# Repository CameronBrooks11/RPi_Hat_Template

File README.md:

# rpi-hat-kicad

KiCad 10 project templates for a Raspberry Pi
[HAT+](https://datasheets.raspberrypi.com/hat/hat-plus-specification.pdf): the
board outline, mounting holes, 40-pin GPIO connector and the ID EEPROM a HAT+
needs, placed, routed and passing DRC, ready to design on.

**Documentation: <https://cameronbrooks11.github.io/rpi-hat-kicad/>**

| Template                      | GPIO connector                                 | Board         |
| ----------------------------- | ---------------------------------------------- | ------------- |
| [`RPi_Hat_THT`](RPi_Hat_THT/) | 2x20 through-hole female header, underneath    | 65 x 56 mm    |
| [`RPi_Hat_SMD`](RPi_Hat_SMD/) | Samtec HLE-120-02 SMD pass-through socket      | 65 x 56.5 mm  |

Each template has the outline from Raspberry Pi's HAT mechanical drawing, four
mounting holes, the GPIO connector J1 with its power pins wired and a global
label (`GPIO2` to `GPIO27`) on every other GPIO pin, and the HAT+ ID EEPROM
placed and routed beside J1. Each carries its own `RPi_Hat` libraries, so a
project opens without installing anything.

- **New HAT:** [create a project from a template](https://cameronbrooks11.github.io/rpi-hat-kicad/getting-started/).
- **Which template:** [through-hole or SMD](https://cameronbrooks11.github.io/rpi-hat-kicad/templates/); it decides how high the board sits above the Pi.
- **Calling it a HAT+:** the [HAT+ checklist](https://cameronbrooks11.github.io/rpi-hat-kicad/hat-plus/) and [programming the ID EEPROM](https://cameronbrooks11.github.io/rpi-hat-kicad/eeprom/).

## Development

With [just](https://just.systems/), Python 3 and KiCad 10's `kicad-cli`,
`just check` is the gate CI runs on every pull request: the two templates'
libraries identical, ERC finding only the 26 GPIO label warnings, and DRC
clean with schematic parity on both. The
[development page](https://cameronbrooks11.github.io/rpi-hat-kicad/development/)
covers changing a template and building the docs.

## Credit

Derived from [RPi_Hat_Template](https://github.com/devbisme/RPi_Hat_Template)
by Dave Vandenbout, which laid both connectors and both outlines over each
other for the user to delete one. The footprints come from his
[RPi_Hat.pretty](https://github.com/devbisme/RPi_Hat.pretty).

## License

MIT. See [LICENSE](LICENSE).

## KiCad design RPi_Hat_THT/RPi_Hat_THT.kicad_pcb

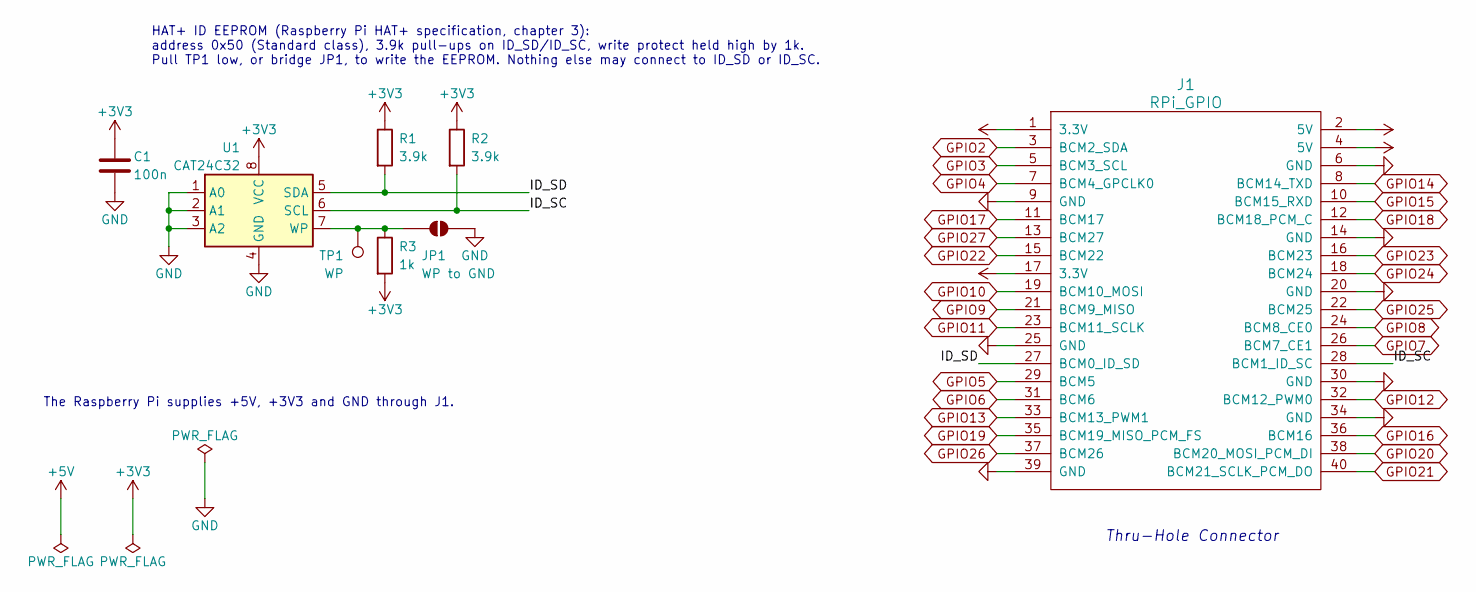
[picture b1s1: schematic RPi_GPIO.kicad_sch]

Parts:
C1: 100n; C_0603_1608Metric
J1: RPi_GPIO; Pin_Header_Straight_2x20
JP1: WP to GND; SolderJumper-2_P1.3mm_Open_RoundedPad1.0x1.5mm
R1, R2: 3.9k; R_0603_1608Metric
R3: 1k; R_0603_1608Metric
TP1: WP; TestPoint_Pad_D1.0mm
U1: CAT24C32; SOIC-8_3.9x4.9mm_P1.27mm

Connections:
+3V3: C1.1, J1.1 (3.3V), J1.17 (3.3V), R1.1, R2.1, R3.2, U1.8 (VCC)
+5V: J1.2 (5V), J1.4 (5V)
/RPi_GPIO/ID_SC: J1.28 (BCM1_ID_SC), R2.2, U1.6 (SCL)
/RPi_GPIO/ID_SD: J1.27 (BCM0_ID_SD), R1.2, U1.5 (SDA)
GND: C1.2, J1.6 (GND), J1.9 (GND), J1.14 (GND), J1.20 (GND), J1.25 (GND), J1.30 (GND), J1.34 (GND), J1.39 (GND), JP1.2 (B), U1.1 (A0), U1.2 (A1), U1.3 (A2), U1.4 (GND)
GPIO2: J1.3 (BCM2_SDA)
GPIO3: J1.5 (BCM3_SCL)
GPIO4: J1.7 (BCM4_GPCLK0)
GPIO5: J1.29 (BCM5)
GPIO6: J1.31 (BCM6)
GPIO7: J1.26 (BCM7_CE1)
GPIO8: J1.24 (BCM8_CE0)
GPIO9: J1.21 (BCM9_MISO)
GPIO10: J1.19 (BCM10_MOSI)
GPIO11: J1.23 (BCM11_SCLK)
GPIO12: J1.32 (BCM12_PWM0)
GPIO13: J1.33 (BCM13_PWM1)
GPIO14: J1.8 (BCM14_TXD)
GPIO15: J1.10 (BCM15_RXD)
GPIO16: J1.36 (BCM16)
GPIO17: J1.11 (BCM17)
GPIO18: J1.12 (BCM18_PCM_C)
GPIO19: J1.35 (BCM19_MISO_PCM_FS)
GPIO20: J1.38 (BCM20_MOSI_PCM_DI)
GPIO21: J1.40 (BCM21_SCLK_PCM_DO)
GPIO22: J1.15 (BCM22)
GPIO23: J1.16 (BCM23)
GPIO24: J1.18 (BCM24)
GPIO25: J1.22 (BCM25)
GPIO26: J1.37 (BCM26)
GPIO27: J1.13 (BCM27)
unnamed: JP1.1 (A), R3.1, TP1.1, U1.7 (WP)

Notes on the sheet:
Thru-Hole Connector
HAT+ ID EEPROM (Raspberry Pi HAT+ specification, chapter 3): address 0x50 (Standard class), 3.9k pull-ups on ID_SD/ID_SC, write protect held high by 1k. Pull TP1 low, or bridge JP1, to write the EEPROM. Nothing else may connect to ID_SD or ID_SC.
The Raspberry Pi supplies +5V, +3V3 and GND through J1.

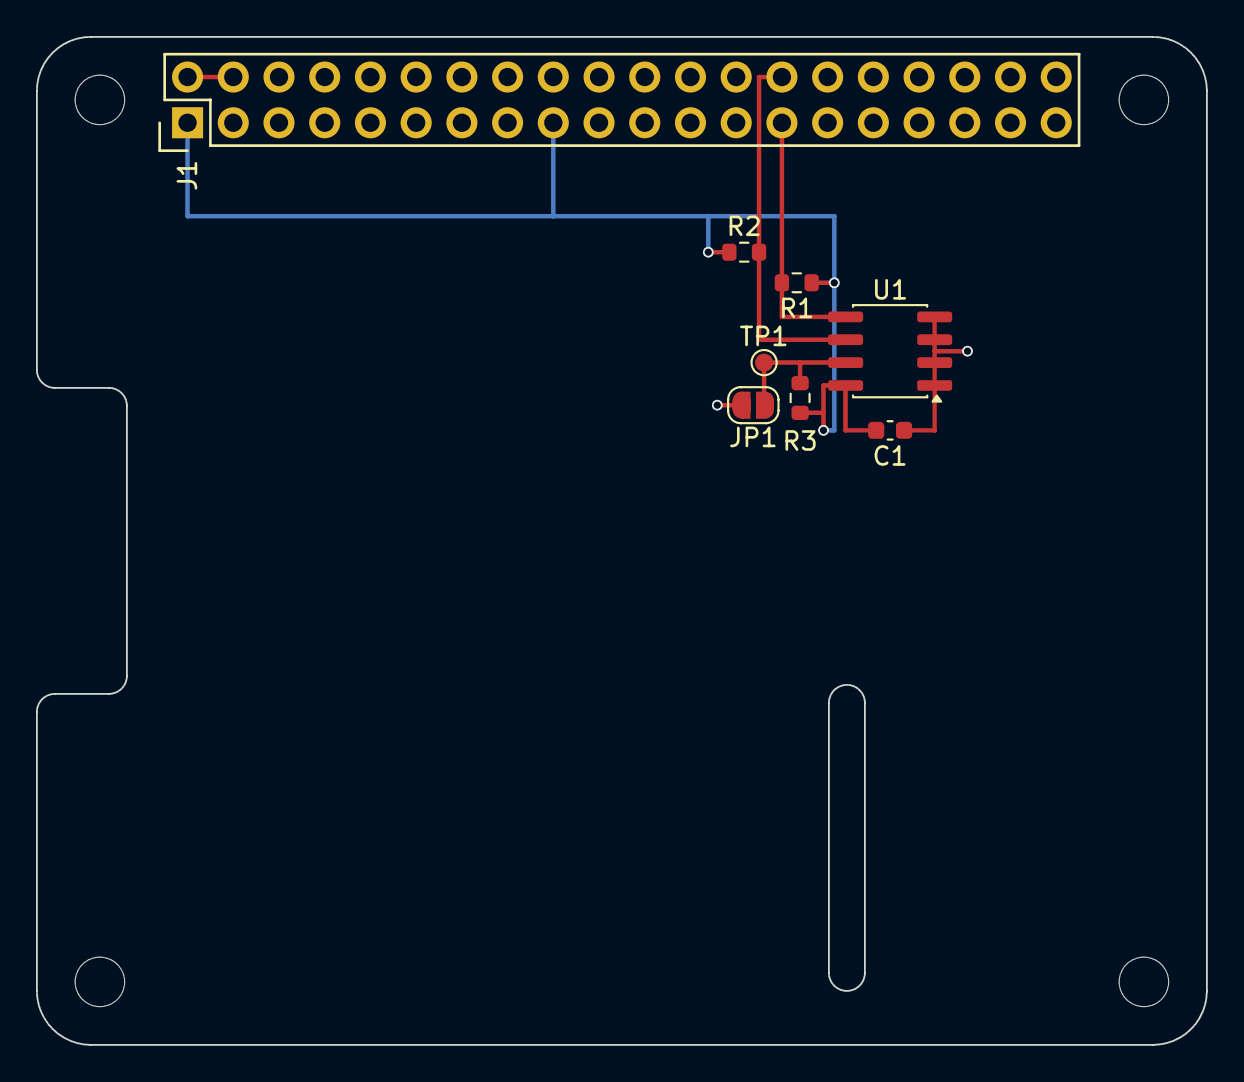
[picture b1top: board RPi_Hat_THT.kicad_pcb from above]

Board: 2 copper layers, 65.0 x 56.0 mm, 12 parts (0 on the bottom side), 6 nets.

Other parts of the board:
H1, H2, H3, H4: RPi_Hat_Mounting_Hole

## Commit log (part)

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2024-03-27 conversion to KiCAD
